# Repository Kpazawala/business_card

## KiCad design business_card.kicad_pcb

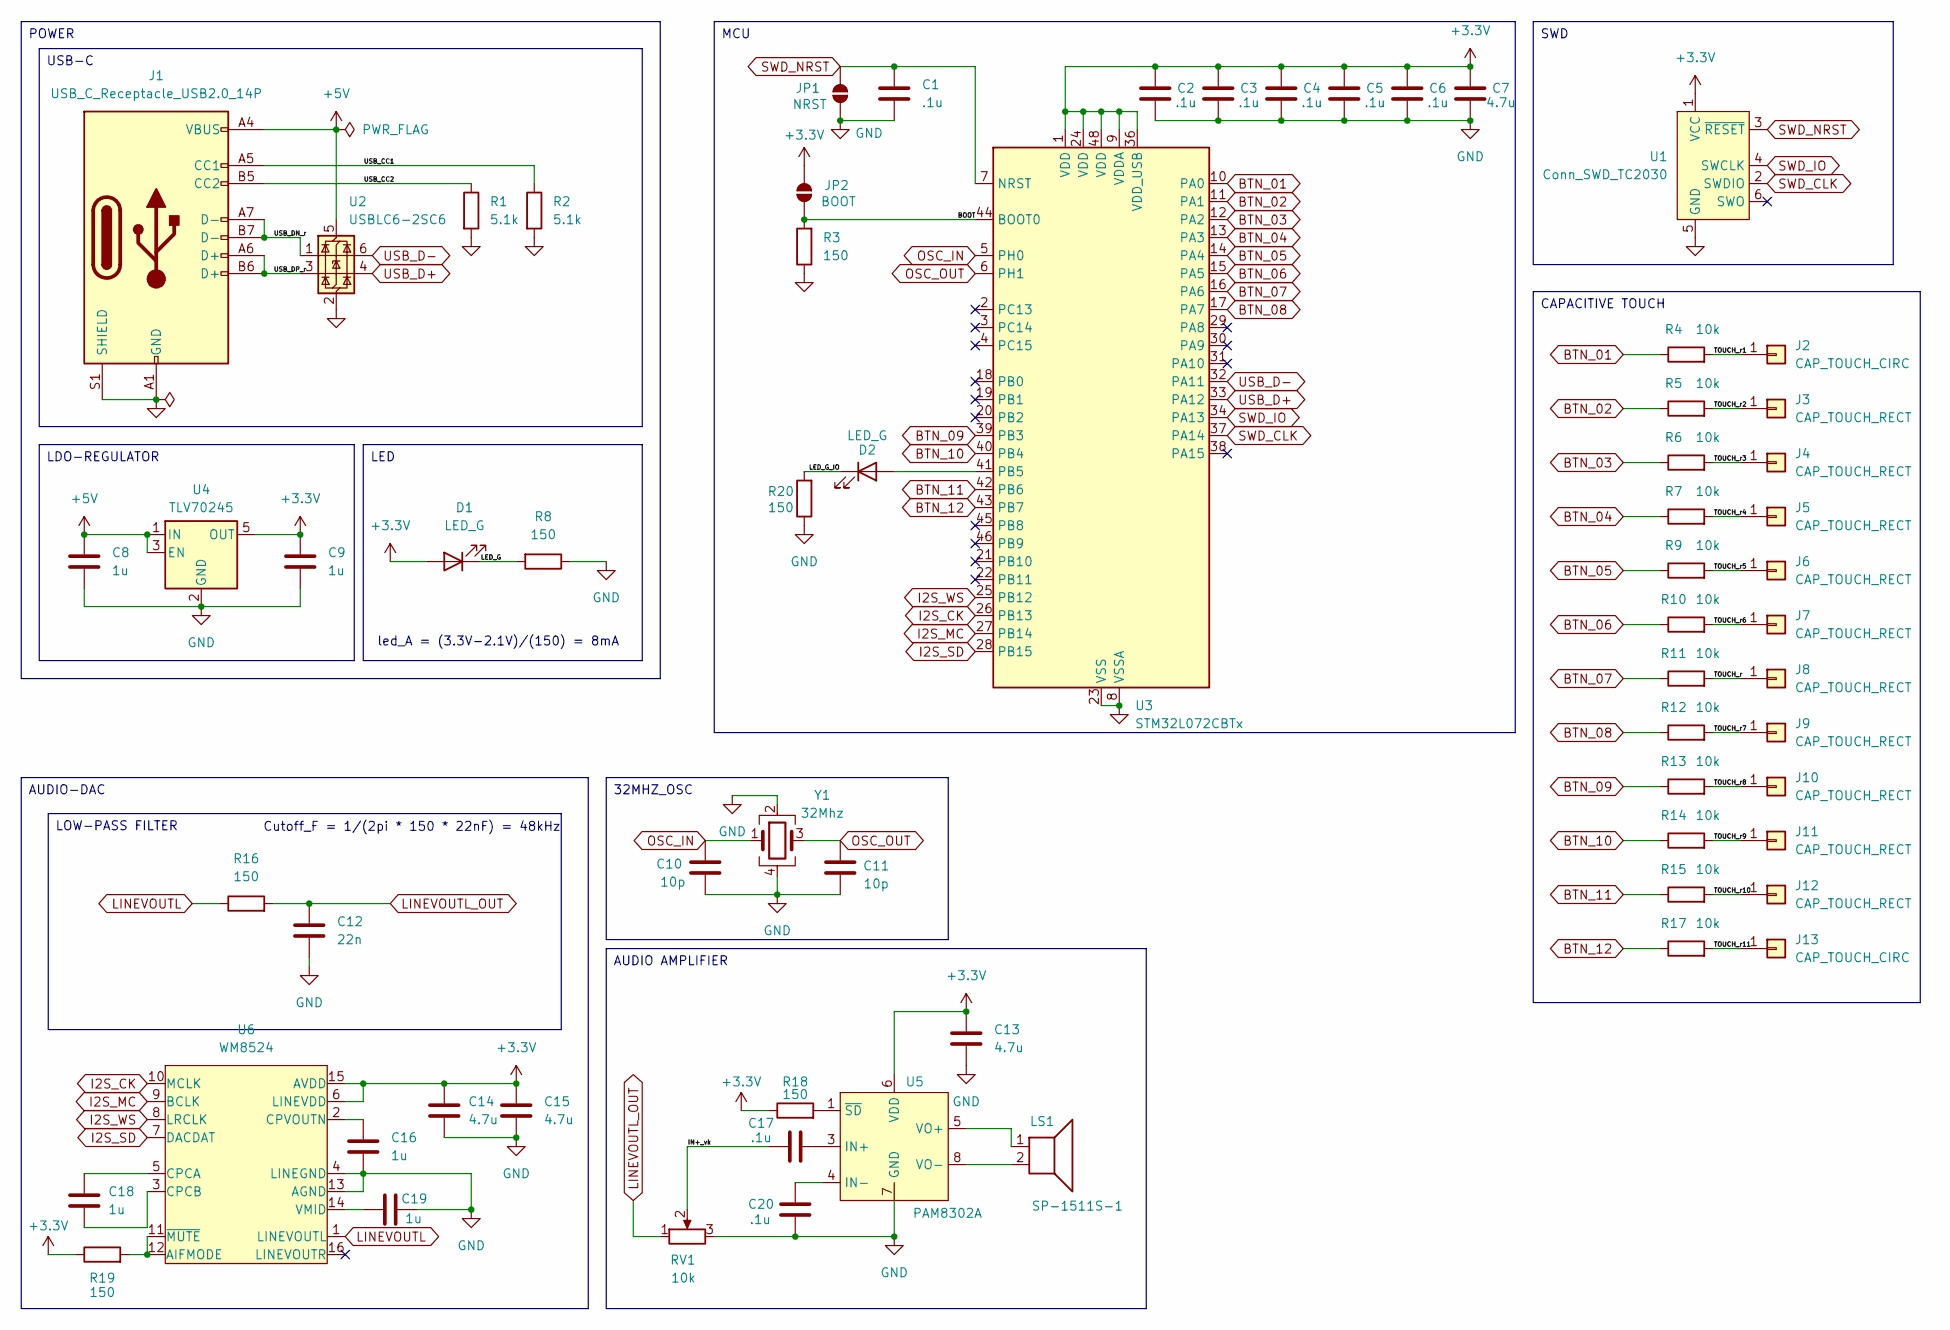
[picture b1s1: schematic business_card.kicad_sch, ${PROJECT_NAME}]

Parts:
C1, C2, C3, C4, C5, C6, C17, C20: .1u; C_0201_0603Metric; MPN GRM033C71C104KE14D
C7, C13, C14, C15: 4.7u; C_0201_0603Metric; MPN GRM035R60J475ME15D
C8, C9, C16, C18, C19: 1u; C_0201_0603Metric; MPN GRM033R61C105ME15D
C10, C11: 10p; C_0201_0603Metric; MPN GRM0335C1E100JA01D
C12: 22n; C_0201_0603Metric; MPN GRM033R61C223KE84D
D1, D2: LED_G; LED_0201_0603Metric; MPN XL-0201UGC
J1: USB_C_Receptacle_USB2.0_14P; USB_C_Receptacle_GCT_USB4105; MPN USB4110-GF-A
J2, J13: CAP_TOUCH_CIRC; Conn_CIRC
J3, J4, J5, J6, J7, J8, J9, J10, J11, J12: CAP_TOUCH_RECT; Conn_RECT
JP1: NRST; SolderJumper-Open_Pad_1.0x1.5mm
JP2: BOOT; SolderJumper-Open_Pad_1.0x1.5mm
LS1: SP-1511S-1; MPN SP-1511S-1
R1, R2: 5.1k; R_0201_0603Metric; MPN RC0201FR-075K1L
R3, R8, R16, R18, R19, R20: 150; R_0201_0603Metric; MPN RC0201FR-07150RL
R4, R5, R6, R7, R9, R10, R11, R12, R13, R14, R15, R17: 10k; R_0201_0603Metric; MPN RC0201FR-0710KL
RV1: 10k; TC33X-2-103E; MPN TC33X-2-103E
U1: Conn_SWD_TC2030
U2: USBLC6-2SC6; SOT-23-6; MPN USBLC6-2SC6
U3: STM32L072CBTx; LQFP-48_7.0x7.0mm_.22mm; MPN STM32L072CBT6
U4: TLV70245; SOT-23-5; MPN TLV7021DBVR
U5: PAM8302A; MSOP-8_3.0x3.0mm; MPN PAM8302AASCR
U6: WM8524; TSSOP-16_5.0x4.4mm; MPN WM8524CGEDT/R
Y1: 32Mhz; CRYSTAL-SMD-4_2.0x1.6mm; MPN END4263D-32M

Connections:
+3.3V: C2.2, C3.2, C4.2, C5.2, C6.2, C7.2, C9.1, C13.1, C14.1, C15.1, D1.2 (A), JP2.1 (A), R18.1, R19.1, U1.1 (VCC), U3.1 (VDD), U3.9 (VDDA), U3.24 (VDD), U3.36 (VDD_USB), U3.48 (VDD), U4.5 (OUT), U5.6 (VDD), U6.6 (LINEVDD), U6.15 (AVDD)
+5V: C8.1, J1.A4 (VBUS), J1.A9 (VBUS), J1.B4 (VBUS), J1.B9 (VBUS), U2.5 (VBUS), U4.1 (IN), U4.3 (EN)
/BOOT: JP2.2 (B), R3.2, U3.44 (BOOT0)
/IN+_vk: C17.1, RV1.2
/LED_G: D1.1 (K), R8.2
/LED_G_IO: D2.1 (K), R20.2
/TOUCH_r: J8.1, R11.2
/TOUCH_r1: J2.1, R4.2
/TOUCH_r2: J3.1, R5.2
/TOUCH_r3: J4.1, R6.2
/TOUCH_r4: J5.1, R7.2
/TOUCH_r5: J6.1, R9.2
/TOUCH_r6: J7.1, R10.2
/TOUCH_r7: J9.1, R12.2
/TOUCH_r8: J10.1, R13.2
/TOUCH_r9: J11.1, R14.2
/TOUCH_r10: J12.1, R15.2
/TOUCH_r11: J13.1, R17.2
/USB_CC1: J1.A5 (CC1), R2.1
/USB_CC2: J1.B5 (CC2), R1.1
/USB_DN_r: J1.A7 (D-), J1.B7 (D-), U2.1 (I/O1)
/USB_DP_r: J1.A6 (D+), J1.B6 (D+), U2.3 (I/O2)
BTN_01: R4.1, U3.10 (PA0)
BTN_02: R5.1, U3.11 (PA1)
BTN_03: R6.1, U3.12 (PA2)
BTN_04: R7.1, U3.13 (PA3)
BTN_05: R9.1, U3.14 (PA4)
BTN_06: R10.1, U3.15 (PA5)
BTN_07: R11.1, U3.16 (PA6)
BTN_08: R12.1, U3.17 (PA7)
BTN_09: R13.1, U3.39 (PB3)
BTN_10: R14.1, U3.40 (PB4)
BTN_11: R15.1, U3.42 (PB6)
BTN_12: R17.1, U3.43 (PB7)
GND: C1.2, C2.1, C3.1, C4.1, C5.1, C6.1, C7.1, C8.2, C9.2, C10.2, C11.2, C12.2, C13.2, C14.2, C15.2, C16.2, C19.2, C20.1, J1.A1 (GND), J1.A12 (GND), J1.B1 (GND), J1.B12 (GND), J1.S1 (SHIELD), JP1.1 (A), R1.2, R2.2, R3.1, R8.1, R20.1, RV1.3, U1.5 (GND), U2.2 (GND), U3.8 (VSSA), U3.23 (VSS), U3.35 (VSS), U3.47 (VSS), U4.2 (GND), U5.7 (GND), U6.4 (LINEGND), U6.13 (AGND), Y1.2, Y1.4
I2S_CK: U3.26 (PB13), U6.10 (MCLK)
I2S_MC: U3.27 (PB14), U6.9 (BCLK)
I2S_SD: U3.28 (PB15), U6.7 (DACDAT)
I2S_WS: U3.25 (PB12), U6.8 (LRCLK)
LINEVOUTL: R16.1, U6.1 (LINEVOUTL)
LINEVOUTL_OUT: C12.1, R16.2, RV1.1
unnamed: D2.2 (A), U3.41 (PB5)
unnamed: C17.2, U5.3 (IN+)
unnamed: C20.2, U5.4 (IN-)
unnamed: LS1.1, U5.5 (VO+)
unnamed: LS1.2, U5.8 (VO-)
unnamed: R18.2, U5.1 (~SD)
unnamed: R19.2, U6.11 (~MUTE), U6.12 (AIFMODE)
unnamed: C18.1, U6.5 (CPCA)
unnamed: C18.2, U6.3 (CPCB)
unnamed: C16.1, U6.2 (CPVOUTN)
unnamed: C19.1, U6.14 (VMID)
OSC_IN: C10.1, U3.5 (PH0), Y1.1
OSC_OUT: C11.1, U3.6 (PH1), Y1.3
SWD_CLK: U1.2 (SWDIO), U3.37 (PA14)
SWD_IO: U1.4 (SWCLK), U3.34 (PA13)
SWD_NRST: C1.1, JP1.2 (B), U1.3 (~RESET), U3.7 (NRST)
USB_D+: U2.4 (I/O2), U3.33 (PA12)
USB_D-: U2.6 (I/O1), U3.32 (PA11)

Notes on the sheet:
Cutoff_F = 1/(2pi * 150 * 22nF) = 48kHz
led_A = (3.3V-2.1V)/(150) = 8mA
AUDIO-DAC
CAPACITIVE TOUCH
LED
SWD
32MHZ_OSC
AUDIO AMPLIFIER
MCU
LDO-REGULATOR
POWER
LOW-PASS FILTER
USB-C

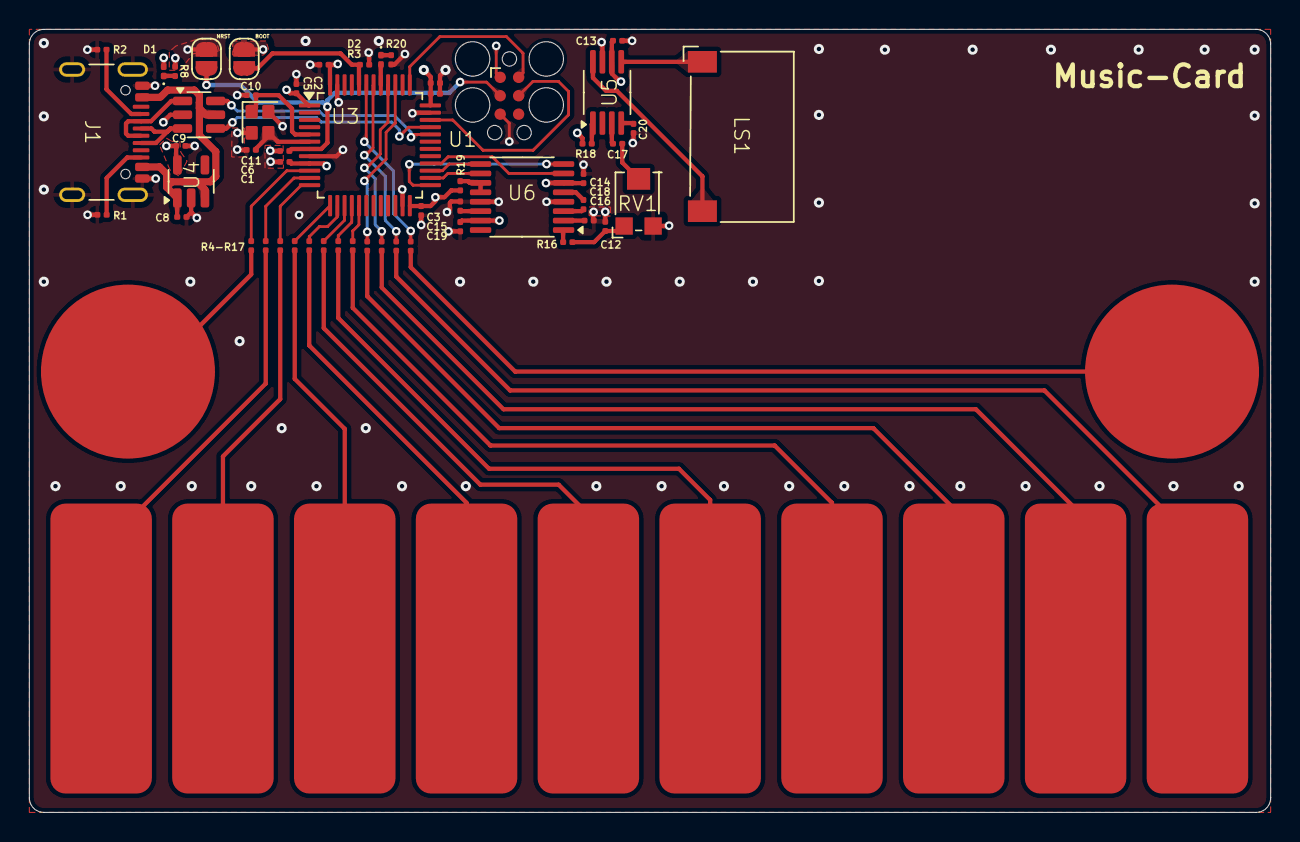
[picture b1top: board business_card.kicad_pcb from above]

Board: 4 copper layers, 85.6 x 54.0 mm, 66 parts (0 on the bottom side), 59 nets.

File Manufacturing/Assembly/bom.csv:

"Reference","Qty","Value","DNP","Exclude from BOM","Footprint","Distributor Link","MPN","Manufacturer"
"R1,R2","2","5.1k","","","0_resistor_smd:R_0201_0603Metric","https://www.digikey.com/en/products/detail/yageo/RC0201FR-07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","RC0201FR-075K1L","YAGEO"
"R3,R8,R16,R18,R19,R20","6","150","","","0_resistor_smd:R_0201_0603Metric","https://www.digikey.com/en/products/detail/yageo/RC0201FR-07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","RC0201FR-07150RL","YAGEO"
"R4,R5,R6,R7,R9,R10,R11,R12,R13,R14,R15,R17","12","10k","","","0_resistor_smd:R_0201_0603Metric","https://www.digikey.com/en/products/detail/yageo/RC0201FR-07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","RC0201FR-0710KL","YAGEO"
"D1,D2","2","LED_G","","","0_led_smd:LED_0201_0603Metric","https://www.digikey.com/en/products/detail/xinglight/XL-0201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","XL-0201UGC","XINGLIGHT"
"U4","1","TLV70245","","","0_package_sot_smd:SOT-23-5","https://www.digikey.com/en/products/detail/texas-instruments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","TLV7021DBVR","Texas Instruments"
"U2","1","USBLC6-2SC6","","","0_package_sot_smd:SOT-23-6","https://www.digikey.com/en/products/detail/stmicroelectronic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","USBLC6-2SC6","STMicroelectronics"
"U3","1","STM32L072CBTx","","","0_package_qfp:LQFP-48_7.0x7.0mm_.22mm","https://www.digikey.com/en/products/detail/stmicroelectronic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","STM32L072CBT6","STMicroelectronics"
"LS1","1","SP-1511S-1","","","0_speaker:SP-1511S-1","https://www.digikey.com/en/products/detail/soberton-inc/SP-1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","SP-1511S-1","Soberton Inc."
"Y1","1","32Mhz","","","0_crystal:CRYSTAL-SMD-4_2.0x1.6mm","https://www.digikey.com/en/products/detail/ndk-nihon-dempa-k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","END4263D-32M","NDK (NIHON DEMPA KOGYO CO., LTD)"
"C7,C13,C14,C15","4","4.7u","","","0_capacitor_smd:C_0201_0603Metric","https://www.digikey.com/en/products/detail/murata-electronic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","GRM035R60J475ME15D","Murata Electronics"
"C12","1","22n","","","0_capacitor_smd:C_0201_0603Metric","https://www.digikey.com/en/products/detail/murata-electronic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","GRM033R61C223KE84D","Murata Electronics"
"C8,C9,C16,C18,C19","5","1u","","","0_capacitor_smd:C_0201_0603Metric","https://www.digikey.com/en/products/detail/murata-electronic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","GRM033R61C105ME15D","Murata Electronics"
"C1,C2,C3,C4,C5,C6,C17,C20","8",".1u","","","0_capacitor_smd:C_0201_0603Metric","https://www.digikey.com/en/products/detail/murata-electronic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","GRM033C71C104KE14D","Murata Electronics"
"C10,C11","2","10p","","","0_capacitor_smd:C_0201_0603Metric","https://www.digikey.com/en/products/detail/murata-electronic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","GRM0335C1E100JA01D","Murata Electronics"
"J1","1","USB_C_Receptacle_USB2.0_14P","","","0_connector_usb:USB_C_Receptacle_GCT_USB4105","https://www.digikey.com/en/products/detail/gct/USB4110-GF-A/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","USB4110-GF-A","GCT"
"U5","1","PAM8302A","","","0_package_so:MSOP-8_3.0x3.0mm","https://www.digikey.com/en/products/detail/diodes-incorporat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","PAM8302AASCR","Diodes Incorporated"
"U6","1","WM8524","","","0_package_so:TSSOP-16_5.0x4.4mm","https://www.digikey.com/en/products/detail/cirrus-logic-inc/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","WM8524CGEDT/R","Cirrus Logic Inc."
"RV1","1","10k","","","0_potentiometer_smd:TC33X-2-103E","https://www.digikey.com/en/products/detail/bourns-inc/TC33X-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","TC33X-2-103E","Bourns Inc."
"U1","1","Conn_SWD_TC2030","","Excluded from BOM","0_connectors:Conn_SWD_TC2030","","",""
"JP2","1","BOOT","","Excluded from BOM","0_jumper:SolderJumper-Open_Pad_1.0x1.5mm","","",""
"JP1","1","NRST","","Excluded from BOM","0_jumper:SolderJumper-Open_Pad_1.0x1.5mm","","",""
"J3,J4,J5,J6,J7,J8,J9,J10,J11,J12","10","CAP_TOUCH_RECT","","Excluded from BOM","0_connectors:Conn_RECT","","",""
"J2,J13","2","CAP_TOUCH_CIRC","","Excluded from BOM","0_connectors:Conn_CIRC","","",""

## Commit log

2025-09-09 Apply .gitignore rules
2025-09-09 Remove
2025-09-09 add folders and remove backups
2025-09-09 remove backups fix
2025-09-09 remove backups fix 2
2025-09-09 remove backups fix 3
2025-09-09 increase ic distance to .22mm
2025-09-10 change IC distnace to .22mm
